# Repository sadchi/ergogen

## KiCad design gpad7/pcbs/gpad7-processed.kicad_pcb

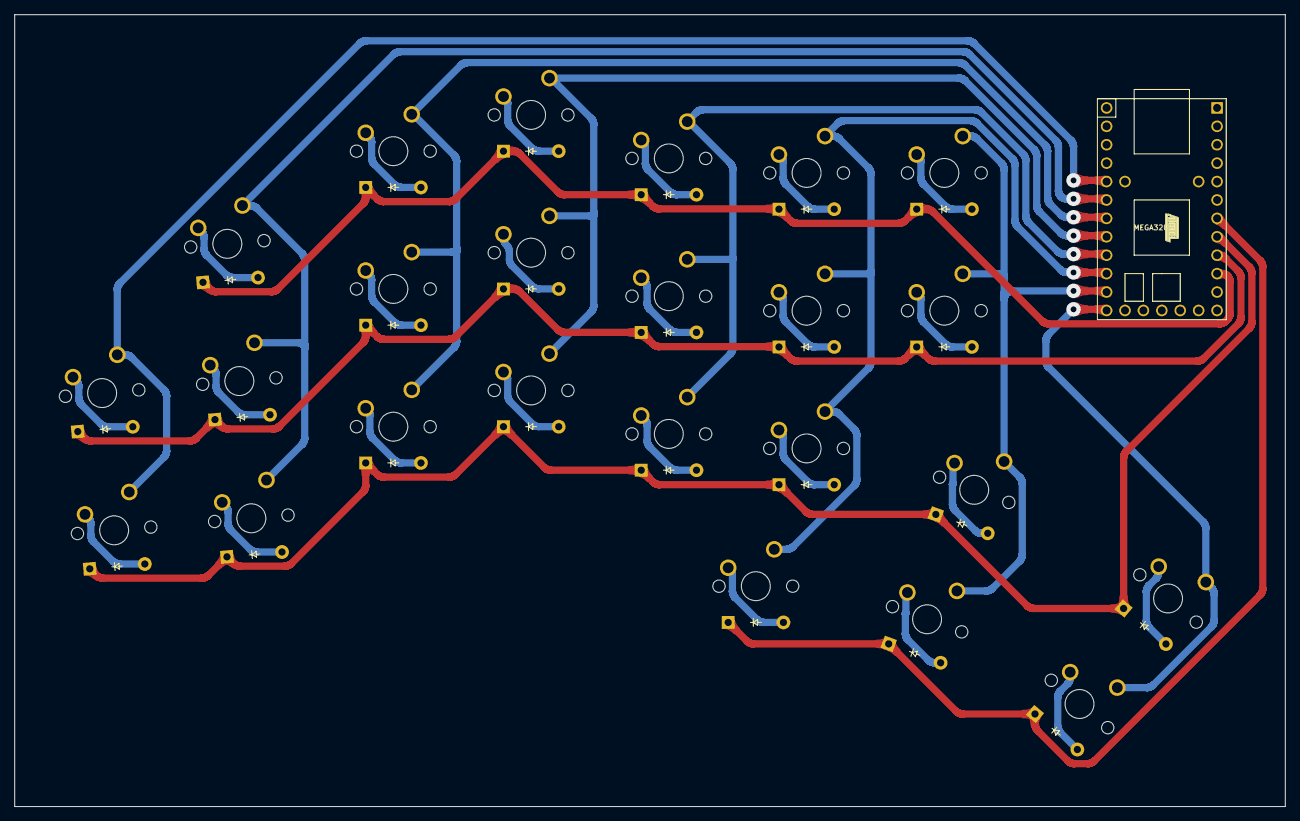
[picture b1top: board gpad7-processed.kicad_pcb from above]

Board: 2 copper layers, 175.3 x 109.2 mm, 49 parts (0 on the bottom side), 38 nets.

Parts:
D1, D2, D3, D4, D5, D6, D7, D8, D9, D10, D11, D12, D13, D14, D15, D16, D17, D18, D19, D20, D21, D22, D23, D24: ComboDiode
MCU1: Teensy2.0
S1, S2, S3, S4, S5, S6, S7, S8, S9, S10, S11, S12, S13, S14, S15, S16, S17, S18, S19, S20, S21, S22, S23, S24: MX

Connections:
B4: MCU1.20, S15.1, S16.1, S17.1, S20.1
B5: MCU1.21, S12.1, S13.1, S14.1
B6: MCU1.22, S9.1, S10.1, S11.1
D0: D20.1, D21.1, D23.1, MCU1.7
D1: D1.1, D3.1, D6.1, D9.1, D12.1, D15.1, D22.1, D24.1, MCU1.8
D2: D2.1, D4.1, D7.1, D10.1, D13.1, D16.1, D18.1, MCU1.9
D3: D5.1, D8.1, D11.1, D14.1, D17.1, D19.1, MCU1.10
D6: MCU1.18, S23.1, S24.1
D7: MCU1.19, S18.1, S19.1, S21.1, S22.1
F5: MCU1.25, S1.1, S2.1
F6: MCU1.24, S3.1, S4.1, S5.1
F7: MCU1.23, S6.1, S7.1, S8.1
GND: MCU1.1, MCU1.15
VCC: MCU1.14, MCU1.29
aux_home: D18.2, S18.2
aux_top: D19.2, S19.2
far_thumb: D23.2, S23.2
far_thumb_secondary: D24.2, S24.2
home_thumb: D21.2, S21.2
home_thumb_secondary: D22.2, S22.2
index_bottom: D12.2, S12.2
index_home: D13.2, S13.2
index_top: D14.2, S14.2
inner_bottom: D15.2, S15.2
inner_home: D16.2, S16.2
inner_top: D17.2, S17.2
middle_bottom: D9.2, S9.2
middle_home: D10.2, S10.2
middle_top: D11.2, S11.2
near_thumb: D20.2, S20.2
outer_bottom: D1.2, S1.2
outer_home: D2.2, S2.2
pinky_bottom: D3.2, S3.2
pinky_home: D4.2, S4.2
pinky_top: D5.2, S5.2
ring_bottom: D6.2, S6.2
ring_home: D7.2, S7.2
ring_top: D8.2, S8.2

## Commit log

2023-06-30 The beginning
2023-06-30 Added teensy2
2023-06-30 Finalized gpad7
2023-06-30 Removed compiled materials
2023-06-30 Upgraded ignore opts
2023-06-30 Changed net list
2023-07-01 Fixed holes radius
2023-07-03 Removed smd pads
2023-07-04 Fixed thumb buttons rotation
2023-07-23 new keyboard added
2023-07-30 noha added
2023-07-31 noha wip
2023-08-26 noha v2 split added
